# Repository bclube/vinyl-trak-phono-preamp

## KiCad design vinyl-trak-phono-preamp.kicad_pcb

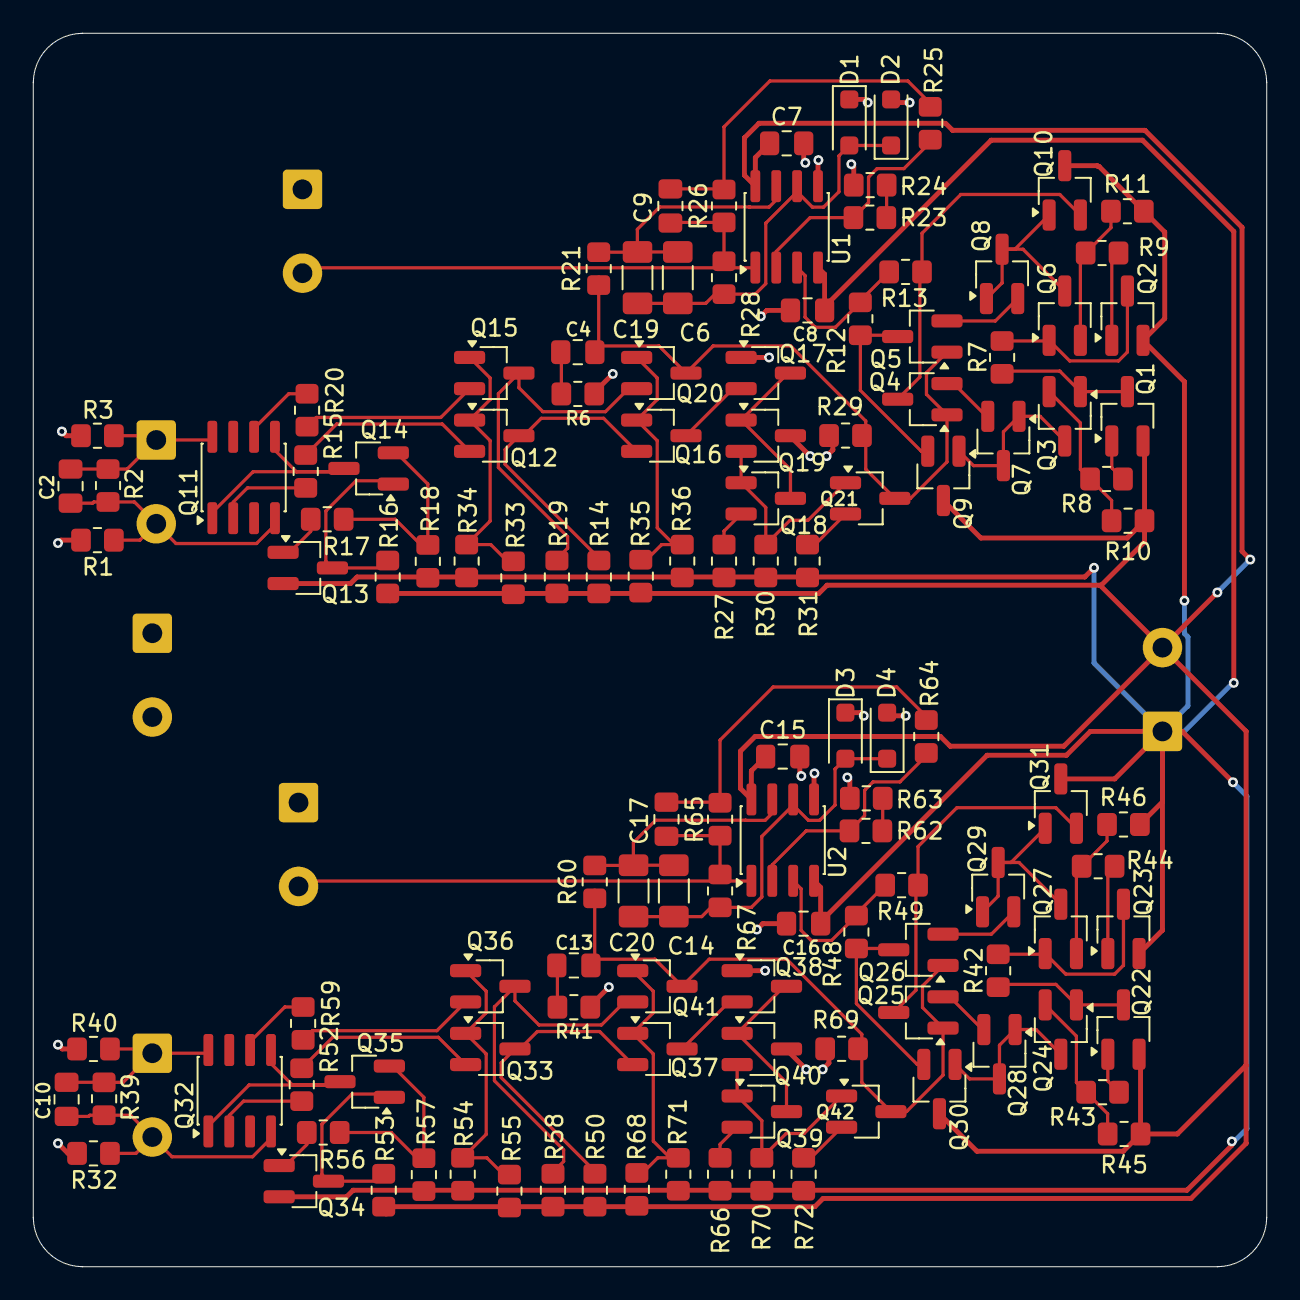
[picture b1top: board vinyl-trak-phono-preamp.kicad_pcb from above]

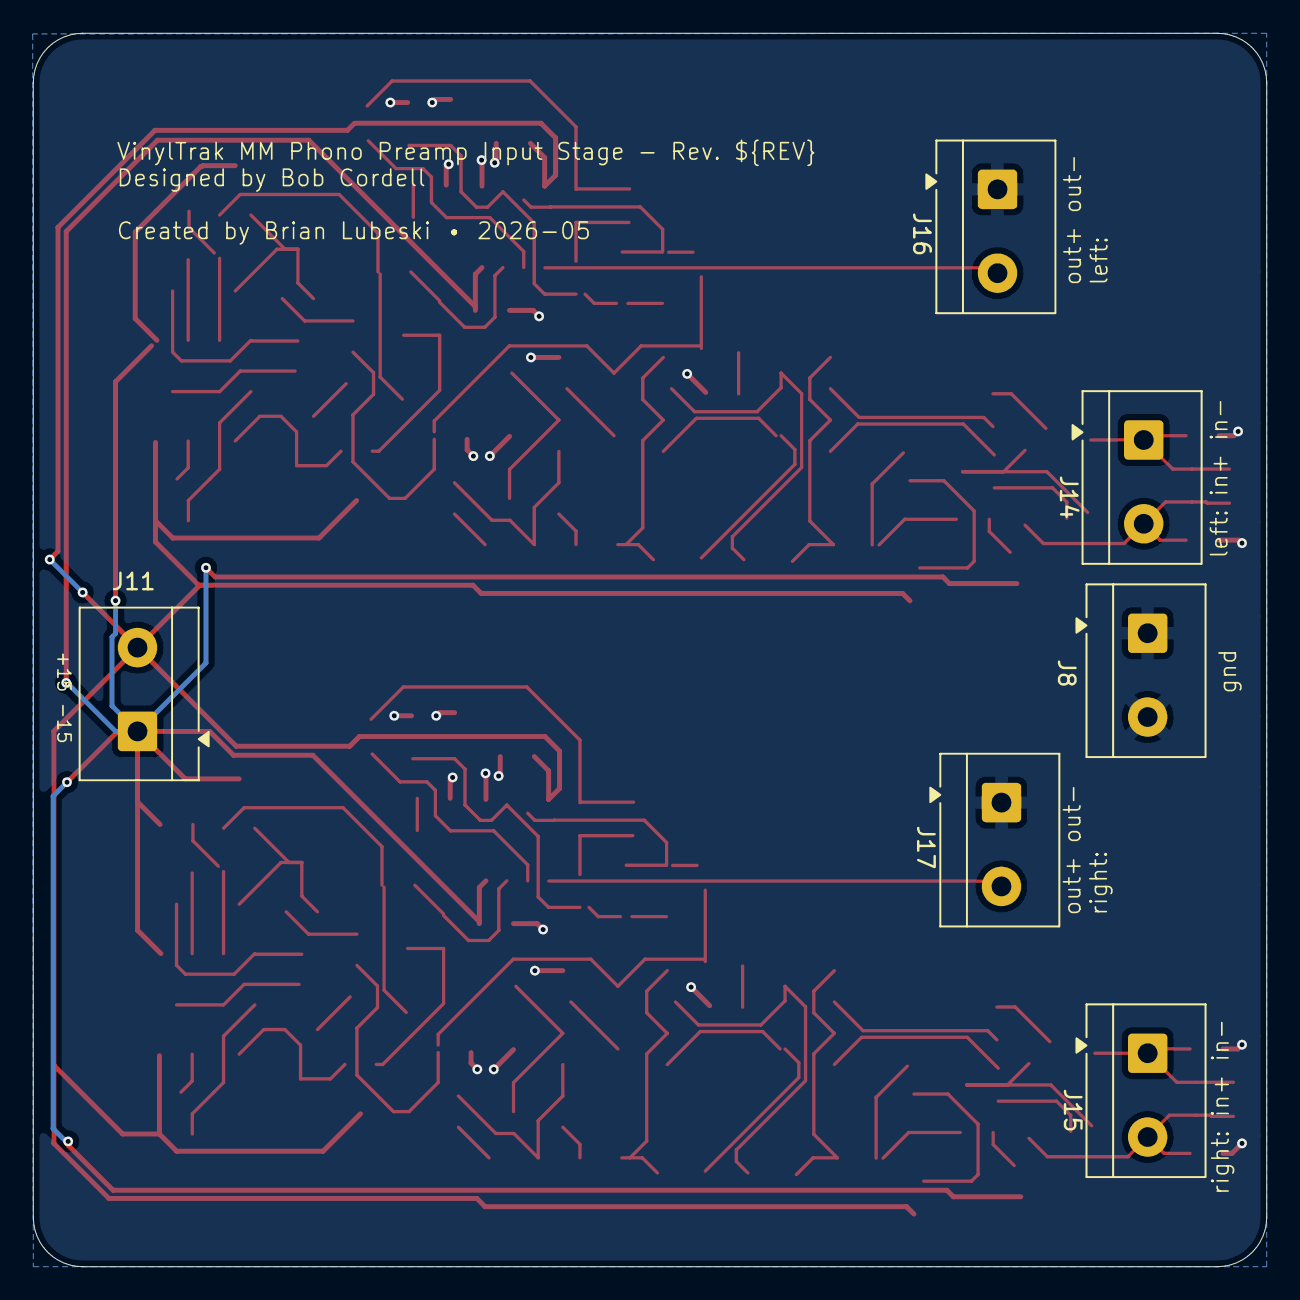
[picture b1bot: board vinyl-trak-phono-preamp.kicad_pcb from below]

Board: 2 copper layers, 75.0 x 75.0 mm, 132 parts (6 on the bottom side), 83 nets.

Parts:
C2, C10: 100p; C_0805_2012Metric_Pad1.18x1.45mm_HandSolder
C4, C13: 0.015u; C_0805_2012Metric_Pad1.18x1.45mm_HandSolder
C6, C14, C19, C20: .47u; C_1206_3216Metric_Pad1.33x1.80mm_HandSolder
C7, C8, C15, C16: 10n; C_0805_2012Metric_Pad1.18x1.45mm_HandSolder
C9, C17: 0.020u; C_0805_2012Metric_Pad1.18x1.45mm_HandSolder
D1, D2, D3, D4: D; D_SOD-123F
J8, J11, J14, J15, J16, J17: Screw_Terminal_01x02; TerminalBlock_4Ucon_1x02_P5mm_Horizontal
Q1, Q3, Q4, Q8, Q10, Q22, Q24, Q25, Q29, Q31: 2N3906; SOT-23_Handsoldering-adjusted-pinout
Q2, Q5, Q6, Q7, Q9, Q13, Q14, Q23, Q26, Q27, Q28, Q30, Q34, Q35: 2N3904; SOT-23_Handsoldering-adjusted-pinout
Q11, Q32: JFE2140D; SOIC-8_3.9x4.9mm_P1.27mm
Q12, Q15, Q18, Q19, Q21, Q33, Q36, Q39, Q40, Q42: 2N5089; SOT-23_Handsoldering-adjusted-pinout
Q16, Q17, Q20, Q37, Q38, Q41: 2N5087; SOT-23_Handsoldering-adjusted-pinout
R1, R3, R32, R40: 100k; R_0805_2012Metric_Pad1.20x1.40mm_HandSolder
R2, R39: 18k; R_0805_2012Metric_Pad1.20x1.40mm_HandSolder
R6, R41: 1k37; R_0805_2012Metric_Pad1.20x1.40mm_HandSolder
R7, R42: 205k; R_0805_2012Metric_Pad1.20x1.40mm_HandSolder
R8, R9, R12, R13, R17, R43, R44, R48, R49, R56: 220; R_0805_2012Metric_Pad1.20x1.40mm_HandSolder
R10, R11, R45, R46: 604; R_0805_2012Metric_Pad1.20x1.40mm_HandSolder
R14, R19, R23, R24, R50, R58, R62, R63: 1k47; R_0805_2012Metric_Pad1.20x1.40mm_HandSolder
R15, R20, R52, R59: 100; R_0805_2012Metric_Pad1.20x1.40mm_HandSolder
R16, R53: 71k5; R_0805_2012Metric_Pad1.20x1.40mm_HandSolder
R18, R57: 160; R_0805_2012Metric_Pad1.20x1.40mm_HandSolder
R21, R34, R54, R60: 56k2; R_0805_2012Metric_Pad1.20x1.40mm_HandSolder
R25, R64: 15k0; R_0805_2012Metric_Pad1.20x1.40mm_HandSolder
R26, R65: 162k; R_0805_2012Metric_Pad1.20x1.40mm_HandSolder
R27, R31, R66, R72: 1k78; R_0805_2012Metric_Pad1.20x1.40mm_HandSolder
R28, R67: 1Meg; R_0805_2012Metric_Pad1.20x1.40mm_HandSolder
R29, R69: 3k83; R_0805_2012Metric_Pad1.20x1.40mm_HandSolder
R30, R70: 47.5k; R_0805_2012Metric_Pad1.20x1.40mm_HandSolder
R33, R55: 20.5k; R_0805_2012Metric_Pad1.20x1.40mm_HandSolder
R35, R68: 33.2k; R_0805_2012Metric_Pad1.20x1.40mm_HandSolder
R36, R71: 115k; R_0805_2012Metric_Pad1.20x1.40mm_HandSolder
U1, U2: OPA2134; SOIC-8_3.9x4.9mm_P1.27mm

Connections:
0: C7.1, C8.1, C15.1, C16.1, D1.1 (K), D2.2 (A), D3.1 (K), D4.2 (A), J8.1, J8.2, J16.1, J17.1, Q17.2 (B), Q19.1 (C), Q38.2 (B), Q40.1 (C), R1.1, R3.2, R6.2, R24.1, R29.2, R32.1, R40.2, R41.2, R63.1, R69.2, U1.5 (+), U2.5 (+)
15+: C7.2, C15.2, J11.2, Q1.3 (E), Q9.1 (C), Q22.3 (E), Q30.1 (C), R10.1, R14.1, R16.1, R19.1, R33.1, R35.1, R45.1, R50.1, R53.1, R55.1, R58.1, R68.1, U1.8 (V+), U2.8 (V+)
15-: C8.2, C16.2, J11.1, Q2.3 (E), Q10.1 (C), Q13.3 (E), Q23.3 (E), Q31.1 (C), Q34.3 (E), R11.2, R18.2, R27.2, R30.2, R31.2, R34.2, R36.2, R46.2, R54.2, R57.2, R66.2, R70.2, R71.2, R72.2, U1.4 (V-), U2.4 (V-)
/l-in+: C2.1, J14.2, Q11.4, R1.2, R2.1
/l-in-: C2.2, J14.1, Q11.8, R2.2, R3.1
/l-out: C9.1, J16.2, R26.2, R28.2, U1.1
/phono-in-left/buffer: R12.2, R13.1, U1.3 (+)
/phono-in-left/buffer+: Q12.1 (C), Q16.3 (E), R14.2
/phono-in-left/buffer-: Q15.1 (C), Q20.3 (E), R19.2
/phono-in-left/cascode: C4.1, Q4.2 (B), Q5.2 (B), Q20.1 (C), Q21.1 (C), R21.1, R29.1
/phono-in-right/buffer: R48.2, R49.1, U2.3 (+)
/phono-in-right/buffer+: Q33.1 (C), Q37.3 (E), R50.2
/phono-in-right/buffer-: Q36.1 (C), Q41.3 (E), R58.2
/phono-in-right/cascode: C13.1, Q25.2 (B), Q26.2 (B), Q41.1 (C), Q42.1 (C), R60.1, R69.1
/r-in+: C10.1, J15.2, Q32.4, R32.2, R39.1
/r-in-: C10.2, J15.1, Q32.8, R39.2, R40.1
/r-out: C17.1, J17.2, R65.2, R67.2, U2.1
unnamed: C4.2, R6.1
unnamed: C9.2, R25.2, R26.1
unnamed: C13.2, R41.1
unnamed: C14.2, C20.2, R60.2, U2.7
unnamed: C17.2, R64.2, R65.1
unnamed: C6.2, C19.2, R21.2, U1.7
unnamed: C6.1, C19.1, D1.2 (A), D2.1 (K), R28.1, U1.6 (-)
unnamed: C14.1, C20.1, D3.2 (A), D4.1 (K), R67.1, U2.6 (-)
unnamed: Q1.2 (B), R8.1
unnamed: Q1.1 (C), Q3.2 (B), R7.1
unnamed: Q2.2 (B), R9.1
unnamed: Q2.1 (C), Q6.2 (B), R7.2
unnamed: Q3.1 (C), Q7.1 (C), Q7.2 (B), Q9.2 (B)
unnamed: Q3.3 (E), R8.2, R10.2
unnamed: Q4.3 (E), Q7.3 (E)
unnamed: Q5.1 (C), Q9.3 (E), R12.1
unnamed: Q5.3 (E), Q8.3 (E)
unnamed: Q6.3 (E), R9.2, R11.1
unnamed: Q6.1 (C), Q8.1 (C), Q8.2 (B), Q10.2 (B)
unnamed: Q4.1 (C), Q10.3 (E), R13.2
unnamed: Q11.2, R15.2
unnamed: Q11.6, R20.2
unnamed: Q12.2 (B), Q15.2 (B), R33.2, R34.1
unnamed: Q12.3 (E), R15.1
unnamed: Q13.2 (B), R17.1
unnamed: Q13.1 (C), Q14.2 (B), R16.2
unnamed: Q11.1, Q11.5, Q14.1 (C)
unnamed: Q14.3 (E), R17.2, R18.1
unnamed: Q15.3 (E), R20.1
unnamed: Q16.2 (B), Q20.2 (B), R35.2, R36.1
unnamed: Q16.1 (C), Q17.3 (E)
unnamed: Q17.1 (C), Q18.1 (C), Q19.2 (B)
unnamed: Q18.2 (B), Q19.3 (E), Q21.2 (B), R30.1
unnamed: Q18.3 (E), R27.1
unnamed: Q21.3 (E), R31.1
unnamed: Q22.2 (B), R43.1
unnamed: Q22.1 (C), Q24.2 (B), R42.1
unnamed: Q23.2 (B), R44.1
unnamed: Q23.1 (C), Q27.2 (B), R42.2
unnamed: Q24.1 (C), Q28.1 (C), Q28.2 (B), Q30.2 (B)
unnamed: Q24.3 (E), R43.2, R45.2
unnamed: Q25.1 (C), Q31.3 (E), R49.2
unnamed: Q25.3 (E), Q28.3 (E)
unnamed: Q26.1 (C), Q30.3 (E), R48.1
unnamed: Q26.3 (E), Q29.3 (E)
unnamed: Q27.1 (C), Q29.1 (C), Q29.2 (B), Q31.2 (B)
unnamed: Q27.3 (E), R44.2, R46.1
unnamed: Q32.2, R52.2
unnamed: Q32.6, R59.2
unnamed: Q33.2 (B), Q36.2 (B), R54.1, R55.2
unnamed: Q33.3 (E), R52.1
unnamed: Q34.2 (B), R56.1
unnamed: Q34.1 (C), Q35.2 (B), R53.2
unnamed: Q32.1, Q32.5, Q35.1 (C)
unnamed: Q35.3 (E), R56.2, R57.1
unnamed: Q36.3 (E), R59.1
unnamed: Q37.2 (B), Q41.2 (B), R68.2, R71.1
unnamed: Q37.1 (C), Q38.3 (E)
unnamed: Q38.1 (C), Q39.1 (C), Q40.2 (B)
unnamed: Q39.2 (B), Q40.3 (E), Q42.2 (B), R70.1
unnamed: Q39.3 (E), R66.1
unnamed: Q42.3 (E), R72.1
unnamed: R23.1, R24.2
unnamed: R62.1, R63.2
unnamed: R23.2, R25.1, U1.2 (-)
unnamed: R62.2, R64.1, U2.2 (-)

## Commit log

2026-05-28 Revision 0.1
2026-06-05 Revision 0.2
    - TH components mounted to PCB back to preserve front space
    - 15+ and 15- lines are kept closer together to reduce noise (even though di/dt is relatively low)
    - Signal path bends around PCB area; DC servo feedback path is much shorter
    - Signal path kept on first layer without jumpers
    - Power distribution is messy
2026-06-17 Revision 0.3 - Fix reverse-wired DC servo - Reduce gain from 40 db to 35 db
